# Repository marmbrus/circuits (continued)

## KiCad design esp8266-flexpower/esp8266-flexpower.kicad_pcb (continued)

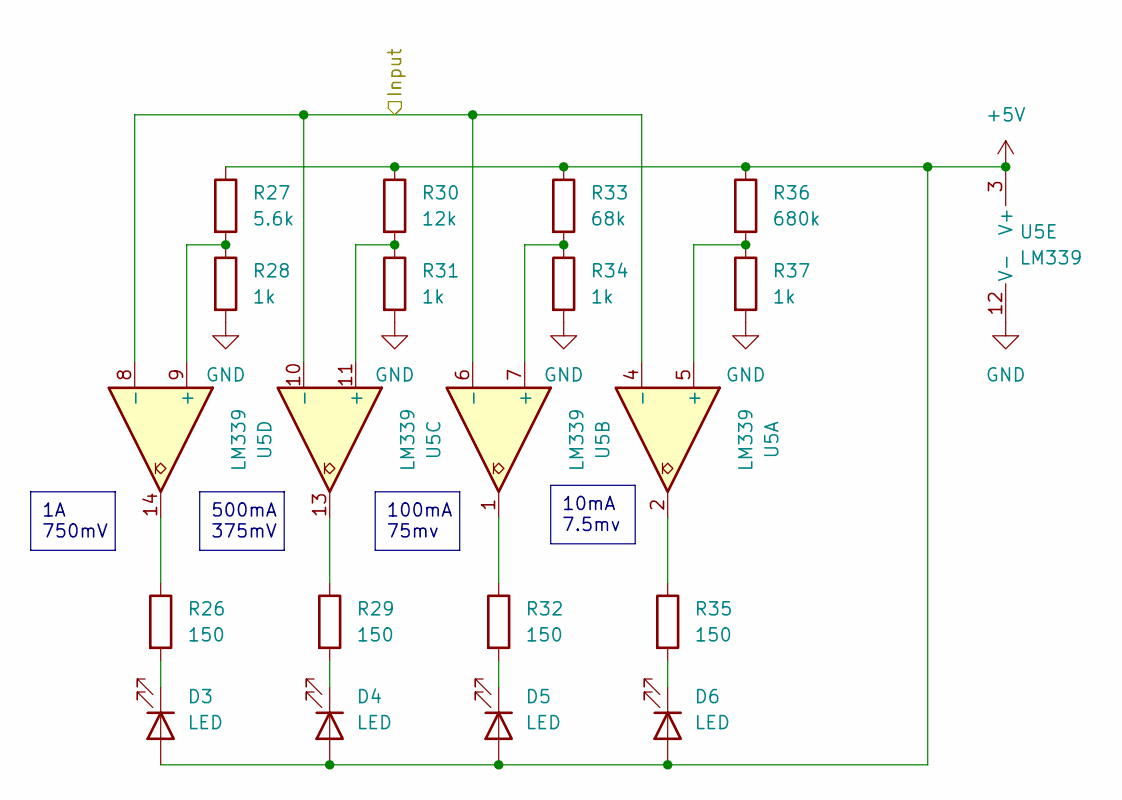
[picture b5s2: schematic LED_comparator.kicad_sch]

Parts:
D3, D4, D5, D6: LED; LED_0603_1608Metric; LCSC Part C2286
R26, R29, R32, R35: 150; R_0603_1608Metric
R27: 5.6k; R_0603_1608Metric
R28, R31, R34, R37: 1k; R_0603_1608Metric
R30: 12k; R_0603_1608Metric
R33: 68k; R_0603_1608Metric
R36: 680k; R_0603_1608Metric
U5: LM339; SOIC-14_3.9x8.7mm_P1.27mm; LCSC Part C350549

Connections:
+5V: D3.2 (A), D4.2 (A), D5.2 (A), D6.2 (A), R27.1, R30.1, R33.1, R36.1, U5.3 (V+); also elsewhere on the board
/LEDComparator/Input: U5.4 (-), U5.6 (-), U5.8 (-), U5.10 (-); also elsewhere on the board
GND: R28.2, R31.2, R34.2, R37.2, U5.12 (V-); also elsewhere on the board
unnamed: D3.1 (K), R26.2
unnamed: D4.1 (K), R29.2
unnamed: D5.1 (K), R32.2
unnamed: D6.1 (K), R35.2
unnamed: R26.1, U5.14
unnamed: R29.1, U5.13
unnamed: R32.1, U5.1
unnamed: R35.1, U5.2
unnamed: R36.2, R37.1, U5.5 (+)
unnamed: R33.2, R34.1, U5.7 (+)
unnamed: R30.2, R31.1, U5.11 (+)
unnamed: R27.2, R28.1, U5.9 (+)

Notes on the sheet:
1A 750mV
100mA 75mv
10mA 7.5mv
500mA 375mV

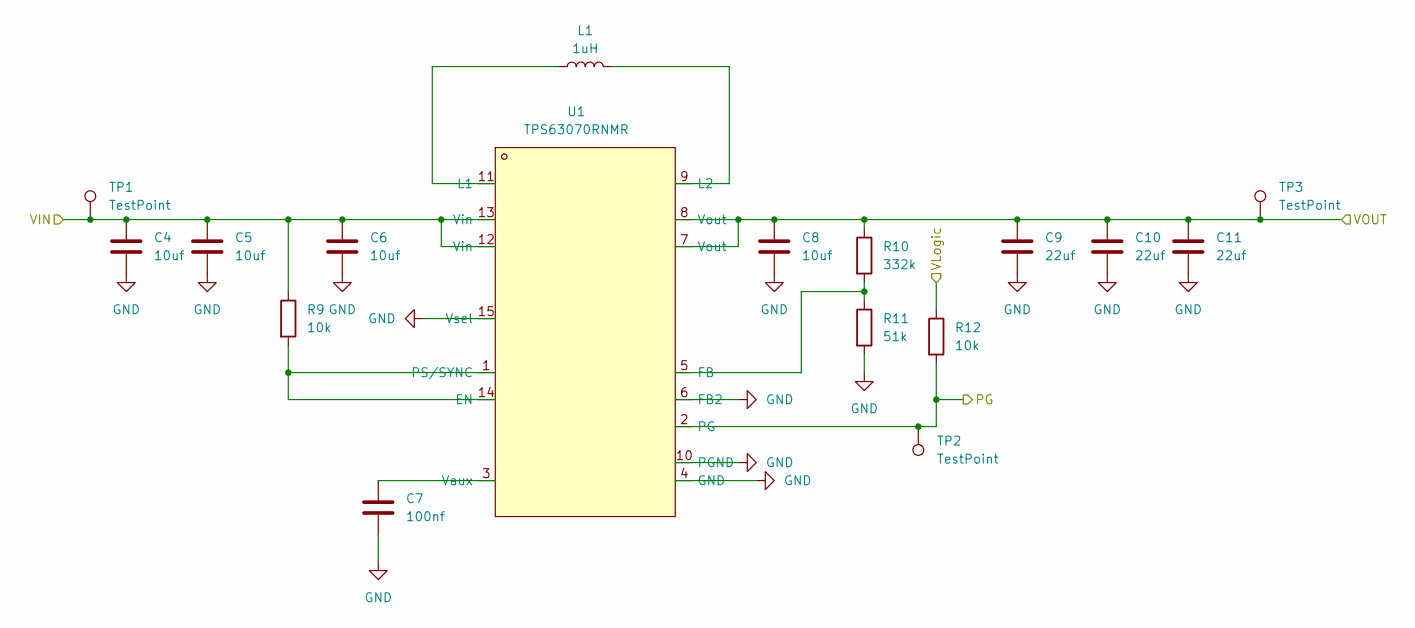
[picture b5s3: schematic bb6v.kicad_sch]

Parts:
C4, C5: 10uf; C_0805_2012Metric
C6, C8: 10uf; C_0603_1608Metric
C7: 100nf; C_0603_1608Metric
C9, C10, C11: 22uf; C_0805_2012Metric
L1: 1uH; L_Coilcraft_XAL4020-XXX; LCSC Part C4555951
R9, R12: 10k; R_0603_1608Metric
R10: 332k; R_0603_1608Metric
R11: 51k; R_0603_1608Metric
TP1, TP2, TP3: TestPoint; Pin_D1.0mm_L10.0mm
U1: TPS63070RNMR; VQFN-HR-15_L3.0-W2.5-P0.50-BL_TPS63070RNMR; LCSC Part C109322

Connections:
+5V: R12.1; also elsewhere on the board
/33Reg/VIN: C8.1, C9.1, C10.1, C11.1, R10.1, TP3.1, U1.7 (Vout), U1.8 (Vout); also elsewhere on the board
/BB6V/PG: R12.2, TP2.1, U1.2 (PG)
/BB6V/VIN: C4.1, C5.1, C6.1, R9.1, TP1.1, U1.12 (Vin), U1.13 (Vin); also elsewhere on the board
GND: C4.2, C5.2, C6.2, C7.2, C8.2, C9.2, C10.2, C11.2, R11.2, U1.4 (GND), U1.6 (FB2), U1.10 (PGND), U1.15 (Vsel); also elsewhere on the board
unnamed: R9.2, U1.1 (PS/SYNC), U1.14 (EN)
unnamed: R10.2, R11.1, U1.5 (FB)
unnamed: L1.1, U1.11 (L1)
unnamed: L1.2, U1.9 (L2)
unnamed: C7.1, U1.3 (Vaux)

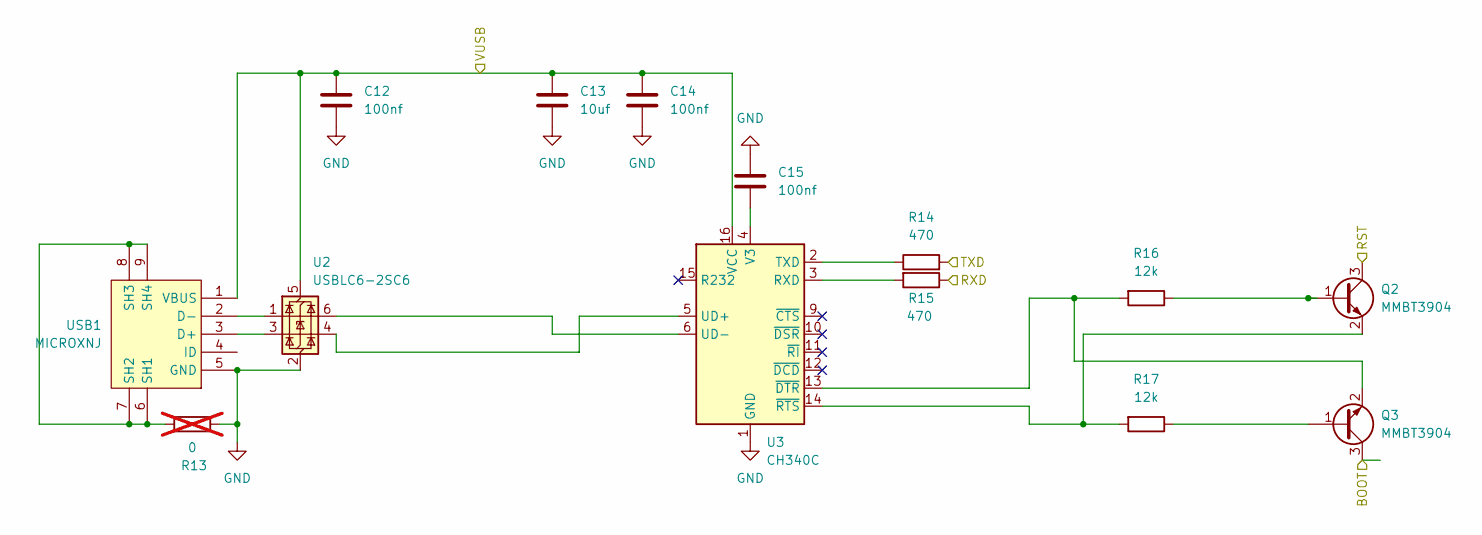
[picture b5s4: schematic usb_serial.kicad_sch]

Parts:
C12, C14, C15: 100nf; C_0603_1608Metric
C13: 10uf; C_0603_1608Metric
Q2, Q3: MMBT3904; SOT-23
R13: 0; R_0603_1608Metric; not fitted
R14, R15: 470; R_0603_1608Metric
R16, R17: 12k; R_0603_1608Metric
U2: USBLC6-2SC6; SOT-23-6
U3: CH340C; SOIC-16_3.9x9.9mm_P1.27mm
USB1: MICROXNJ; MICRO-USB-SMD_MICROXNJ; LCSC Part C404969

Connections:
/ESP12F/BOOT: Q3.3 (C); also elsewhere on the board
/ESP12F/RST: Q2.3 (C); also elsewhere on the board
/ESP12F/RXD: R14.2; also elsewhere on the board
/ESP12F/TXD: R15.1; also elsewhere on the board
/PP3V16V/VIN: C12.1, C13.1, C14.1, U2.5 (VBUS), U3.16 (VCC), USB1.1 (VBUS); also elsewhere on the board
GND: C12.2, C13.2, C14.2, C15.1, R13.2, U2.2 (GND), U3.1 (GND), USB1.5 (GND); also elsewhere on the board
unnamed: Q2.1 (B), R16.1
unnamed: Q2.2 (E), R17.2, U3.14 (~RTS)
unnamed: Q3.1 (B), R17.1
unnamed: Q3.2 (E), R16.2, U3.13 (~DTR)
unnamed: R15.2, U3.3 (RXD)
unnamed: R14.1, U3.2 (TXD)
unnamed: U2.4 (I/O2), U3.5 (UD+)
unnamed: U2.6 (I/O1), U3.6 (UD-)
unnamed: C15.2, U3.4 (V3)
unnamed: U2.3 (I/O2), USB1.3 (D+)
unnamed: U2.1 (I/O1), USB1.2 (D-)
unnamed: R13.1, USB1.6 (SH1), USB1.7 (SH2), USB1.8 (SH3), USB1.9 (SH4)

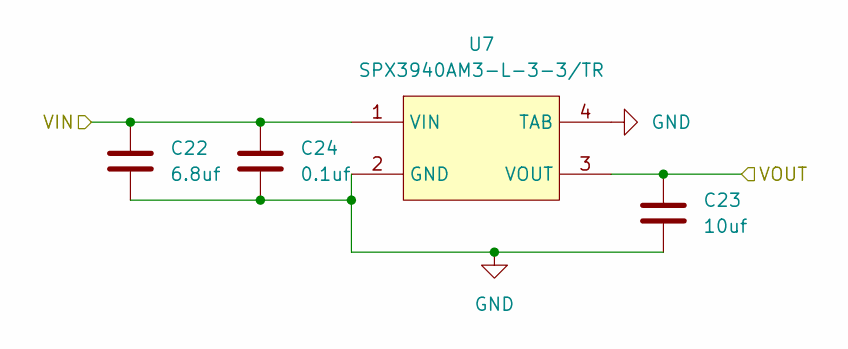
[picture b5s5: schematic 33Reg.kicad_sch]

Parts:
C22: 6.8uf; C_0603_1608Metric
C23: 10uf; C_0603_1608Metric
C24: 0.1uf; C_0603_1608Metric
U7: SPX3940AM3-L-3-3/TR; SOT-223-3_L6.5-W3.4-P2.30-LS7.0-BR; LCSC Part C48252

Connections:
/33Reg/VIN: C22.1, C24.1, U7.1 (VIN); also elsewhere on the board
/33Reg/VOUT: C23.1, U7.3 (VOUT); also elsewhere on the board
GND: C22.2, C23.2, C24.2, U7.2 (GND), U7.4 (TAB); also elsewhere on the board

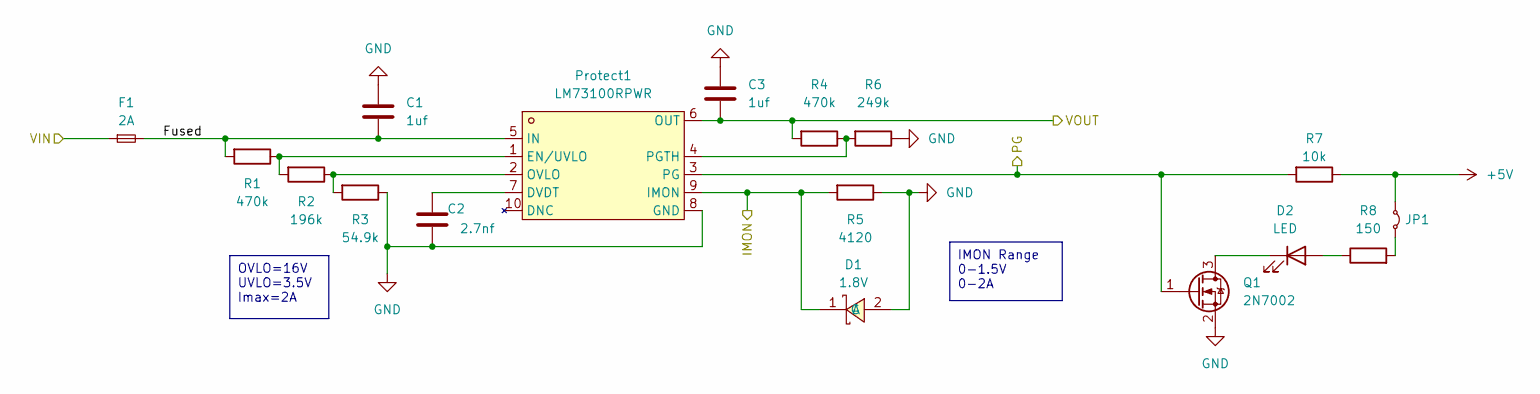
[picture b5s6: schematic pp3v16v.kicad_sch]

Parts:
C1, C3: 1uf; C_0603_1608Metric
C2: 2.7nf; C_0603_1608Metric
D1: 1.8V; SOD-123_L2.7-W1.6-LS3.7-RD; LCSC Part C150464
D2: LED; LED_0603_1608Metric; LCSC Part C2286
F1: 2A; Fuse_1206_3216Metric; LCSC Part C2924939
JP1: JP1; SolderJumper-2_P1.3mm_Bridged_Pad1.0x1.5mm
Protect1: LM73100RPWR; VQFN-10_L2.0-W2.0-P0.45-TL; LCSC Part C3210761
Q1: 2N7002; SOT-23
R1, R4: 470k; R_0603_1608Metric
R2: 196k; R_0603_1608Metric
R3: 54.9k; R_0603_1608Metric
R5: 4120; R_0603_1608Metric
R6: 249k; R_0603_1608Metric
R7: 10k; R_0603_1608Metric
R8: 150; R_0603_1608Metric

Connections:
+5V: JP1.1 (A), R7.1; also elsewhere on the board
/BB6V/VIN: C3.2, Protect1.6 (OUT), R4.2; also elsewhere on the board
/PP3V16V/Fused: C1.2, F1.2, Protect1.5 (IN), R1.2
/PP3V16V/IMON: D1.1 (C), Protect1.9 (IMON), R5.2
/PP3V16V/PG: Protect1.3 (PG), Q1.1 (G), R7.2
/PP3V16V/VIN: F1.1; also elsewhere on the board
GND: C1.1, C2.2, C3.1, D1.2 (A), Protect1.8 (GND), Q1.2 (S), R3.1, R5.1, R6.1; also elsewhere on the board
unnamed: D2.2 (A), R8.1
unnamed: D2.1 (K), Q1.3 (D)
unnamed: JP1.2 (B), R8.2
unnamed: C2.1, Protect1.7 (DVDT)
unnamed: Protect1.1 (EN/UVLO), R1.1, R2.2
unnamed: Protect1.2 (OVLO), R2.1, R3.2
unnamed: Protect1.4 (PGTH), R4.1, R6.2

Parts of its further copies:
C19, C21: 1uf; C_0603_1608Metric
C20: 2.7nf; C_0603_1608Metric
D7: 1.8V; SOD-123_L2.7-W1.6-LS3.7-RD; LCSC Part C150464
D8: LED; LED_0603_1608Metric; LCSC Part C2286
F2: 2A; Fuse_1206_3216Metric; LCSC Part C2924939
JP2: JP1; SolderJumper-2_P1.3mm_Bridged_Pad1.0x1.5mm
Protect2: LM73100RPWR; VQFN-10_L2.0-W2.0-P0.45-TL; LCSC Part C3210761
Q4: 2N7002; SOT-23
R38, R41: 470k; R_0603_1608Metric
R39: 196k; R_0603_1608Metric
R40: 54.9k; R_0603_1608Metric
R42: 4120; R_0603_1608Metric
R43: 249k; R_0603_1608Metric
R44: 10k; R_0603_1608Metric
R45: 150; R_0603_1608Metric

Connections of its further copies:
+5V: JP2.1 (A), R44.1; also elsewhere on the board
/BB6V/VIN: C21.2, Protect2.6 (OUT), R41.2; also elsewhere on the board
/LEDComparator/Input: D7.1 (C), Protect2.9 (IMON), R42.2; also elsewhere on the board
/PP3V16V1/Fused: C19.2, F2.2, Protect2.5 (IN), R38.2
/PP3V16V1/PG: Protect2.3 (PG), Q4.1 (G), R44.2
/PP3V16V1/VIN: F2.1; also elsewhere on the board
GND: C19.1, C20.2, C21.1, D7.2 (A), Protect2.8 (GND), Q4.2 (S), R40.1, R42.1, R43.1; also elsewhere on the board
unnamed: D8.2 (A), R45.1
unnamed: D8.1 (K), Q4.3 (D)
unnamed: JP2.2 (B), R45.2
unnamed: C20.1, Protect2.7 (DVDT)
unnamed: Protect2.1 (EN/UVLO), R38.1, R39.2
unnamed: Protect2.2 (OVLO), R39.1, R40.2
unnamed: Protect2.4 (PGTH), R41.1, R43.2

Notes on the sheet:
IMON Range 0-1.5V 0-2A
OVLO=16V UVLO=3.5V Imax=2A

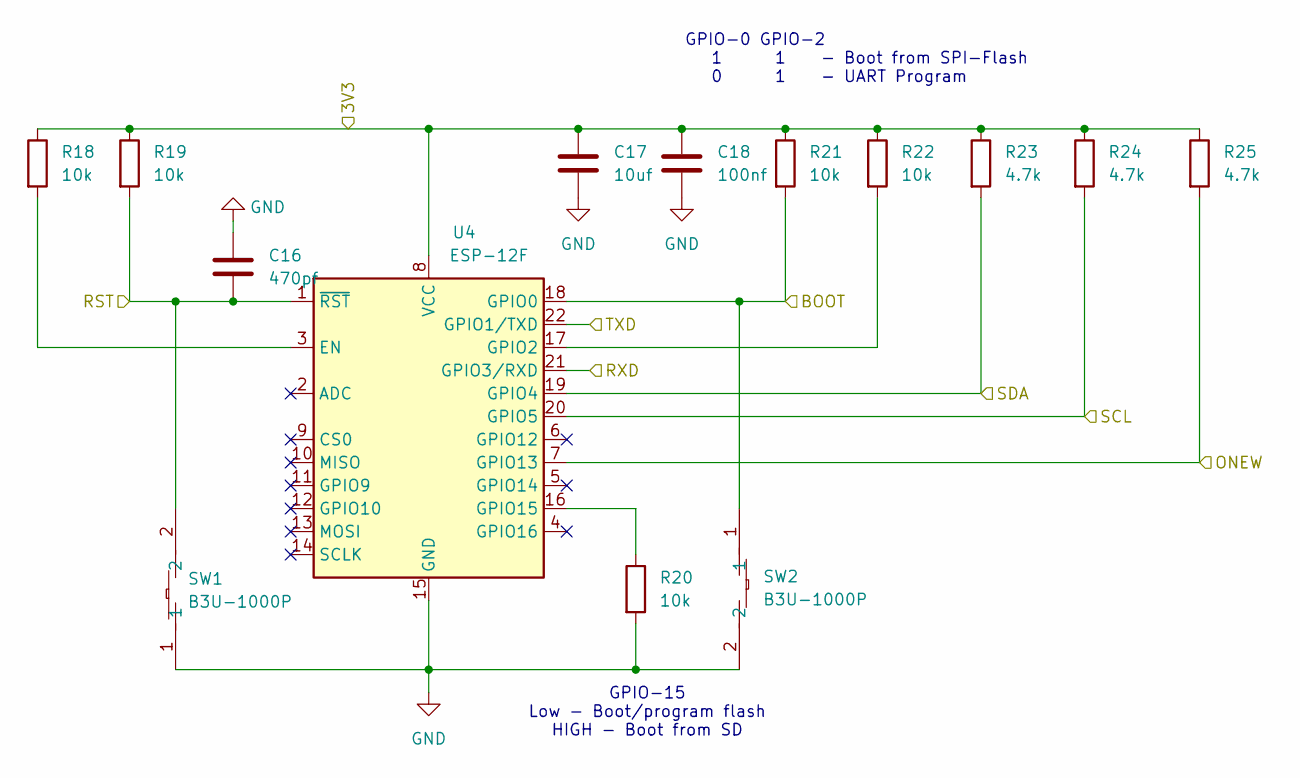
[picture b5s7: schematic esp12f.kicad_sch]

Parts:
C16: 470pf; C_0603_1608Metric
C17: 10uf; C_0603_1608Metric
C18: 100nf; C_0603_1608Metric
R18, R19, R20, R21, R22: 10k; R_0603_1608Metric
R23, R24, R25: 4.7k; R_0603_1608Metric
SW1, SW2: B3U-1000P; KEY-SMD_B3U-1000PM; LCSC Part C231329
U4: ESP-12F; ESP-12E

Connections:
/33Reg/VOUT: C17.1, C18.1, R18.1, R19.1, R21.1, R22.1, R23.1, R24.1, R25.1, U4.8 (VCC); also elsewhere on the board
/ESP12F/BOOT: R21.2, SW2.1, U4.18 (GPIO0); also elsewhere on the board
/ESP12F/ONEW: R25.2, U4.7 (GPIO13); also elsewhere on the board
/ESP12F/RST: C16.2, R19.2, SW1.2, U4.1 (~RST); also elsewhere on the board
/ESP12F/RXD: U4.21 (GPIO3/RXD); also elsewhere on the board
/ESP12F/SCL: R24.2, U4.20 (GPIO5); also elsewhere on the board
/ESP12F/SDA: R23.2, U4.19 (GPIO4); also elsewhere on the board
/ESP12F/TXD: U4.22 (GPIO1/TXD); also elsewhere on the board
GND: C16.1, C17.2, C18.2, R20.2, SW1.1, SW2.2, U4.15 (GND); also elsewhere on the board
unnamed: R18.2, U4.3 (EN)
unnamed: R22.2, U4.17 (GPIO2)
unnamed: R20.1, U4.16 (GPIO15)

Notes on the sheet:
GPIO-15 Low - Boot/program flash HIGH - Boot from SD
GPIO-0 GPIO-2 1 1 - Boot from SPI-Flash 0 1 - UART Program

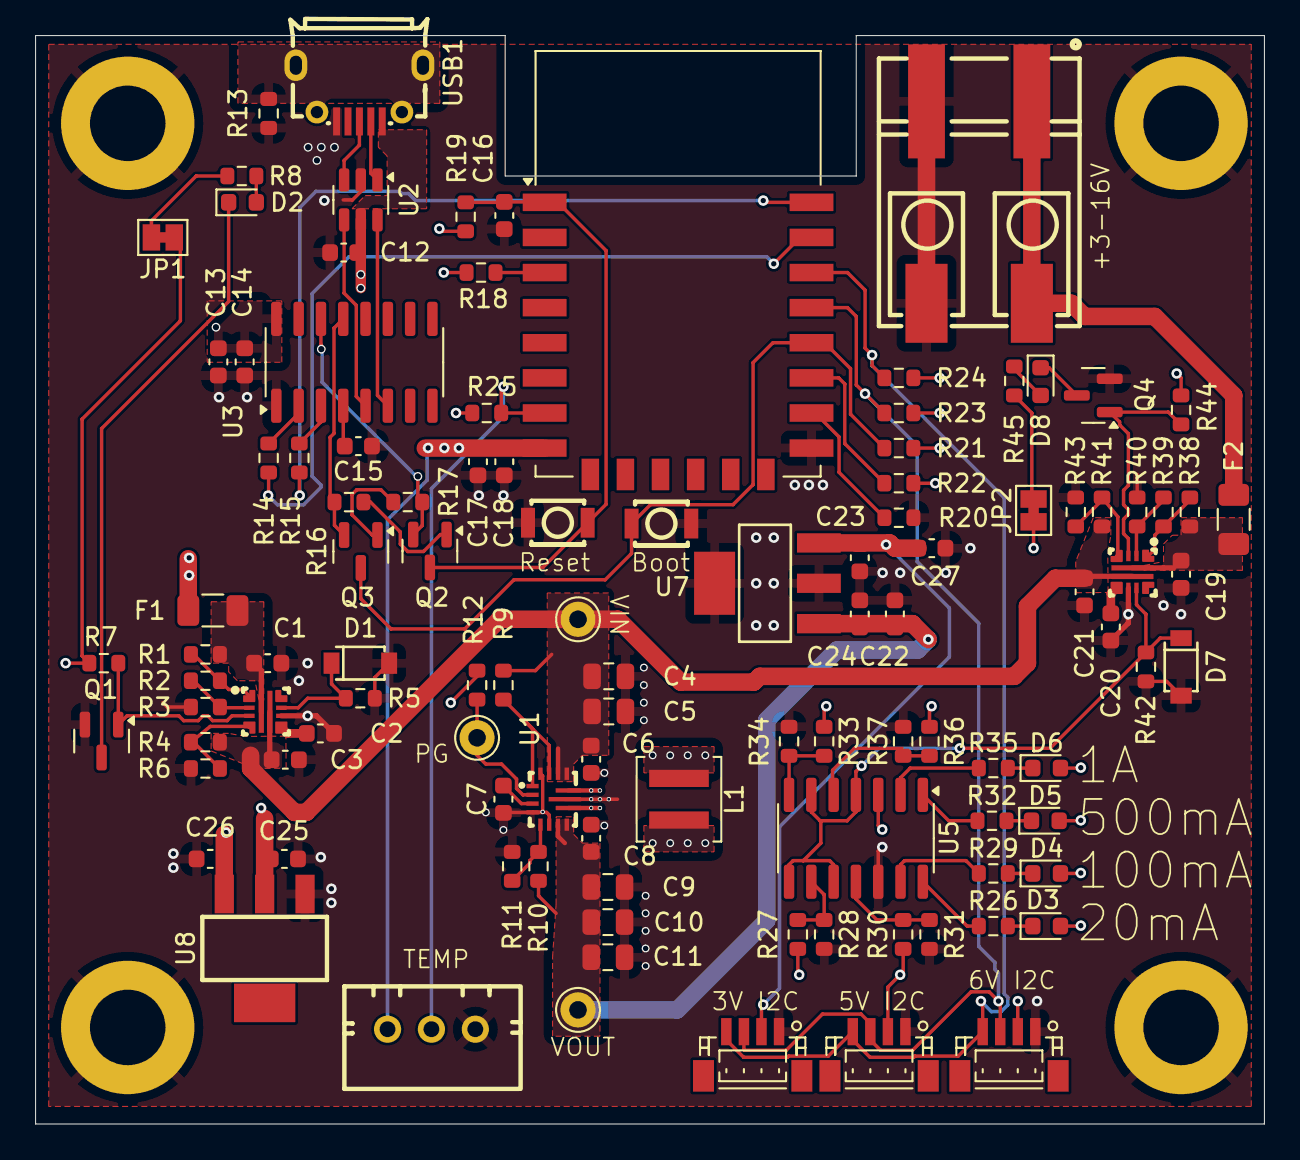
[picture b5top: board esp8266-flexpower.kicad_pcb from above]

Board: 4 copper layers, 70.0 x 62.0 mm, 113 parts (0 on the bottom side), 67 nets.

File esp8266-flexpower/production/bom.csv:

Designator,Footprint,Quantity,Value,LCSC Part #
"C1, C19, C21, C3",0603,4,1uf,
"C10, C11, C9",0805,3,22uf,
"C12, C14, C15, C18, C7",0603,5,100nf,
"C13, C17, C23, C25, C26, C6, C8",0603,7,10uf,
C16,0603,1,470pf,
"C2, C20",0603,2,2.7nf,
C22,0603,1,6.8uf,
C24,0603,1,0.1uf,
C27,0603,1,47uf,
"C4, C5",0805,2,10uf,
"CN1, CN2, CN3",CONN-SMD_BM04B-SRSS-TB,3,BM04B-SRSS-TB(LF)(SN),C160390
"D1, D7",SOD-123_L2.7-W1.6-LS3.7-RD,2,1.8V,C150464
"D2, D3, D4, D5, D6, D8",0603,6,LED,C2286
"F1, F2",1206,2,2A,C2924939
"JP1, JP2",SolderJumper-2_P1.3mm_Bridged_Pad1.0x1.5mm,2,JP1,
L1,L_Coilcraft_XAL4020-XXX,1,1uH,C4555951
"Protect1, Protect2",VQFN-10_L2.0-W2.0-P0.45-TL,2,LM73100RPWR,C3210761
"Q1, Q4",SOT-23,2,2N7002,
"Q2, Q3",SOT-23,2,MMBT3904,
"R1, R38, R4, R41",0603,4,470k,
R10,0603,1,332k,
R11,0603,1,51k,
"R12, R18, R19, R20, R21, R22, R44, R7, R9",0603,9,10k,
"R14, R15",0603,2,470,
"R16, R17, R30",0603,3,12k,
"R2, R39",0603,2,196k,
"R23, R24, R25",0603,3,4.7k,
"R26, R29, R32, R35, R45, R8",0603,6,150,
R27,0603,1,5.6k,
"R28, R31, R34, R37",0603,4,1k,
"R3, R40",0603,2,54.9k,
R33,0603,1,68k,
R36,0603,1,680k,
"R42, R5",0603,2,4120,
"R43, R6",0603,2,249k,
"SW1, SW2",KEY-SMD_B3U-1000PM,2,B3U-1000P,C231329
U1,VQFN-HR-15_L3.0-W2.5-P0.50-BL_TPS63070RNMR,1,TPS63070RNMR,C109322
U2,SOT-23-6,1,USBLC6-2SC6,
U3,SOIC-16_3.9x9.9mm_P1.27mm,1,CH340C,
U4,ESP-12E,1,ESP-12F,
U5,SOIC-14_3.9x8.7mm_P1.27mm,1,LM339,C350549
U6,CONN-SMD_2061-602-998-404,1,2061-602/998-404,C2765058
U7,SOT-223-3_L6.5-W3.4-P2.30-LS7.0-BR,1,SPX3940AM3-L-3-3/TR,C48252
U8,SOT-223_L6.7-W3.5-P2.30-BR,1,AMS1117-5.0_C347223,C347223
U9,CONN-TH_3P-P2.50_A2501WV2-3P,1,B3B-XH-A(LF)(SN),C144394
USB1,MICRO-USB-SMD_MICROXNJ,1,MICROXNJ,C404969

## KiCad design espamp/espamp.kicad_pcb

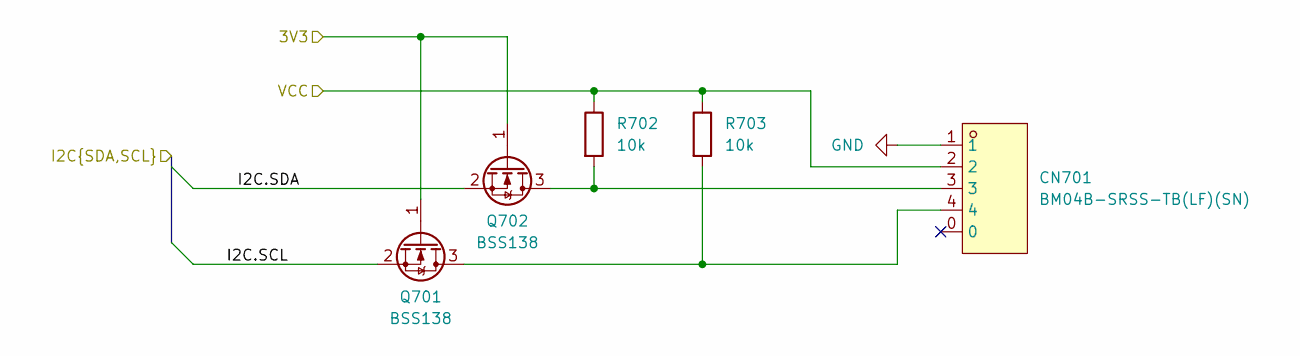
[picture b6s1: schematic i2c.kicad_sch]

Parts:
CN701: BM04B-SRSS-TB(LF)(SN); CONN-SMD_BM04B-SRSS-TB; LCSC Part C160390
Q701, Q702: BSS138; SOT-23
R702, R703: 10k; R_0603_1608Metric

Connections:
/3v3/3v3: Q701.1 (G), Q702.1 (G); also elsewhere on the board
/5V: CN701.2, R702.1, R703.1; also elsewhere on the board
/amp/I2C.SCL: Q701.2 (S); also elsewhere on the board
/amp/I2C.SDA: Q702.2 (S); also elsewhere on the board
GND: CN701.1; also elsewhere on the board
unnamed: CN701.4, Q701.3 (D), R703.2
unnamed: CN701.3, Q702.3 (D), R702.2

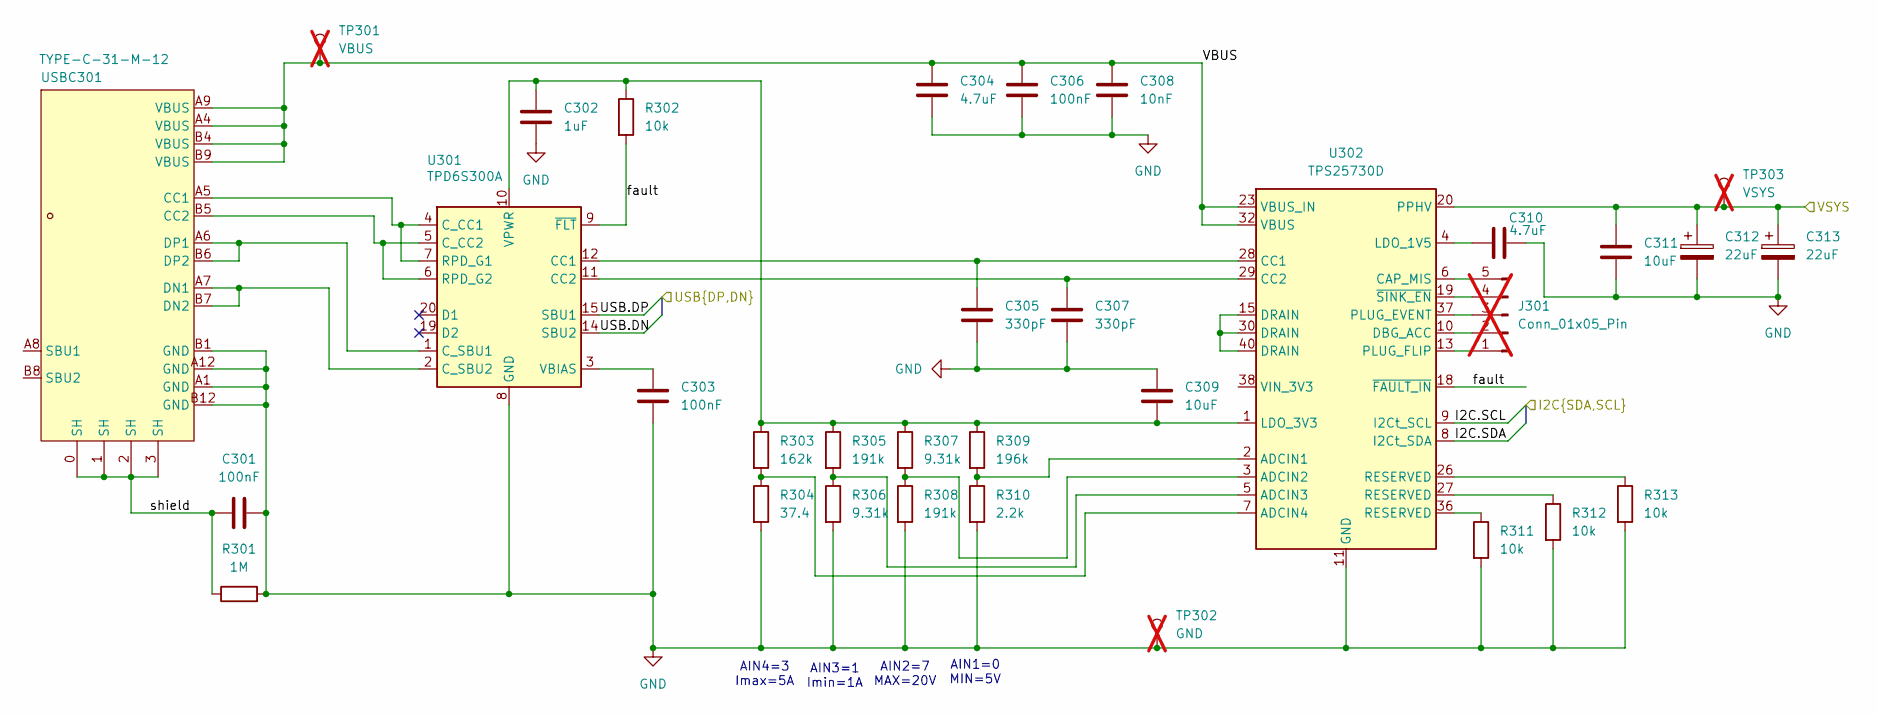
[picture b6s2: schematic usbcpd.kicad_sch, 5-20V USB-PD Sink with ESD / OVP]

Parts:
C301, C303, C306: 100nF; C_0603_1608Metric
C302: 1uF; C_0603_1608Metric
C304, C310: 4.7uF; C_0603_1608Metric
C305, C307: 330pF; C_0603_1608Metric
C308: 10nF; C_0603_1608Metric
C309, C311: 10uF; C_0603_1608Metric
C312, C313: 22uF; C_Elec_5x5.8; LCSC Part C336246
J301: Conn_01x05_Pin; PinSocket_1x05_P1.00mm_Vertical; not fitted
R301: 1M; R_0603_1608Metric
R302, R311, R312, R313: 10k; R_0603_1608Metric
R303: 162k; R_0603_1608Metric
R304: 37.4; R_0603_1608Metric
R305, R308: 191k; R_0603_1608Metric
R306, R307: 9.31k; R_0603_1608Metric
R309: 196k; R_0603_1608Metric
R310: 2.2k; R_0603_1608Metric
TP301: VBUS; Pin_D1.0mm_L10.0mm; not fitted
TP302: GND; Pin_D1.0mm_L10.0mm; not fitted
TP303: VSYS; Pin_D1.0mm_L10.0mm; not fitted
U301: TPD6S300A; WQFN-20-1EP_3x3mm_P0.4mm_EP1.7x1.7mm_ThermalVias
U302: TPS25730D; Texas_REF0038A_WQFN-38-2EP_6x4mm_P0.4
USBC301: TYPE-C-31-M-12; USB-C_SMD-TYPE-C-31-M-12; LCSC Part C165948

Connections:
/20V: C311.1, C312.1, C313.1, TP303.1, U302.20 (PPHV); also elsewhere on the board
/amp/I2C.SCL: U302.9 (I2Ct_SCL); also elsewhere on the board
/amp/I2C.SDA: U302.8 (I2Ct_SDA); also elsewhere on the board
/esp32/USB.DN: U301.14 (SBU2); also elsewhere on the board
/esp32/USB.DP: U301.15 (SBU1); also elsewhere on the board
/usbcpd/VBUS: C304.1, C306.1, C308.1, TP301.1, U302.23 (VBUS_IN), U302.32 (VBUS), USBC301.A4 (VBUS), USBC301.A9 (VBUS), USBC301.B4 (VBUS), USBC301.B9 (VBUS)
/usbcpd/fault: R302.2, U301.9 (~FLT), U302.18 (~FAULT_IN)
/usbcpd/shield: C301.1, R301.1, USBC301.0 (SH), USBC301.1 (SH), USBC301.2 (SH), USBC301.3 (SH)
GND: C301.2, C302.2, C303.2, C304.2, C305.2, C306.2, C307.2, C308.2, C309.2, C310.2, C311.2, C312.2, C313.2, R301.2, R304.2, R306.2, R308.2, R310.2, R311.2, R312.2, R313.2, TP302.1, U301.8 (GND), U301.13 (GND), U301.16 (GND), U301.17 (GND), U301.18 (GND), U301.21 (GND), U302.11 (GND), U302.12 (GND), U302.14 (GND), U302.16 (GND), U302.17 (GND), U302.31 (GND), U302.34 (GND), U302.39 (GND), USBC301.A1 (GND), USBC301.A12 (GND), USBC301.B1 (GND), USBC301.B12 (GND); also elsewhere on the board
unnamed: J301.1, U302.13 (PLUG_FLIP)
unnamed: J301.2, U302.10 (DBG_ACC)
unnamed: J301.3, U302.37 (PLUG_EVENT)
unnamed: J301.4, U302.19 (~SINK_EN)
unnamed: J301.5, U302.6 (CAP_MIS)
unnamed: R311.1, U302.36 (RESERVED)
unnamed: R312.1, U302.27 (RESERVED)
unnamed: R313.1, U302.26 (RESERVED)
unnamed: C305.1, U301.12 (CC1), U302.28 (CC1)
unnamed: C307.1, U301.11 (CC2), U302.29 (CC2)
unnamed: U301.4 (C_CC1), U301.7 (RPD_G1), USBC301.A5 (CC1)
unnamed: U301.5 (C_CC2), U301.6 (RPD_G2), USBC301.B5 (CC2)
unnamed: U301.1 (C_SBU1), USBC301.A6 (DP1), USBC301.B6 (DP2)
unnamed: U301.2 (C_SBU2), USBC301.A7 (DN1), USBC301.B7 (DN2)
unnamed: C303.1, U301.3 (VBIAS)
unnamed: C302.1, C309.1, R302.1, R303.1, R305.1, R307.1, R309.1, U301.10 (VPWR), U302.1 (LDO_3V3)
unnamed: R309.2, R310.1, U302.2 (ADCIN1)
unnamed: R307.2, R308.1, U302.3 (ADCIN2)
unnamed: R305.2, R306.1, U302.5 (ADCIN3)
unnamed: R303.2, R304.1, U302.7 (ADCIN4)
unnamed: U302.15 (DRAIN), U302.30 (DRAIN), U302.40 (DRAIN)
unnamed: C310.1, U302.4 (LDO_1V5)

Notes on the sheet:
AIN1=0 MIN=5V
AIN3=1 Imin=1A
AIN4=3 Imax=5A
AIN2=7 MAX=20V

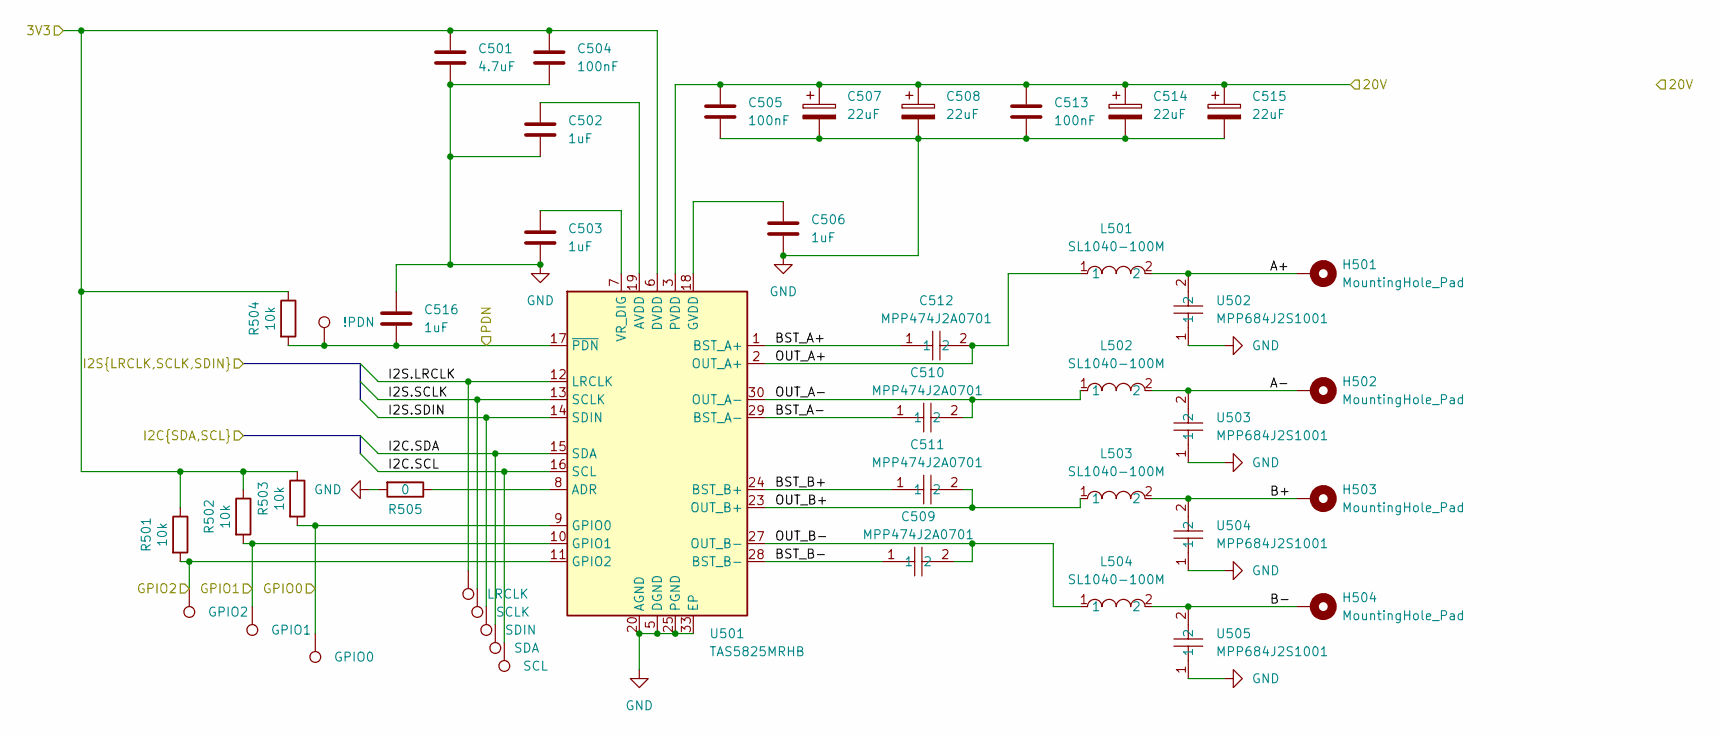
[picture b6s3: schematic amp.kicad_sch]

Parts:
C501: 4.7uF; C_0603_1608Metric
C502, C503, C506, C516: 1uF; C_0603_1608Metric
C504, C505, C513: 100nF; C_0603_1608Metric
C507, C508, C514, C515: 22uF; C_Elec_5x5.8; LCSC Part C336246
C509, C510, C511, C512: MPP474J2A0701; CAP-TH_L9.5-W3.7-P7.50-D0.5; LCSC Part C3019096
H501, H502, H503, H504: MountingHole_Pad; MountingHole_4mm_Pad_Via
L501, L502, L503, L504: SL1040-100M; IND-SMD_L11.0-W10.2; LCSC Part C22463839
R501, R502, R503, R504: 10k; R_0603_1608Metric
R505: 0; R_0603_1608Metric
TP501, TP502, TP503, TP504, TP505, TP506, TP507, TP508, TP509: LabeledTestPoint
U501: TAS5825MRHB; VQFN-32-1EP_5x5mm_P0.5mm_EP3.1x3.1mm
U502, U503, U504, U505: MPP684J2S1001; CAP-TH_L12.0-W5.8-P10.00-D0.6; LCSC Part C3019017

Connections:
/3v3/3v3: C501.1, C504.1, R501.1, R502.1, R503.1, R504.1, U501.6 (DVDD); also elsewhere on the board
/20V: C505.1, C507.1, C508.1, C513.1, C514.1, C515.1, U501.3 (PVDD), U501.4 (PVDD), U501.21 (PVDD), U501.22 (PVDD); also elsewhere on the board
/amp/A+: H501.1, L501.2, U502.2
/amp/A-: H502.1, L502.2, U503.2
/amp/B+: H503.1, L503.2, U504.2
/amp/B-: H504.1, L504.2, U505.2
/amp/BST_A+: C512.1, U501.1 (BST_A+)
/amp/BST_A-: C510.1, U501.29 (BST_A-)
/amp/BST_B+: C511.1, U501.24 (BST_B+)
/amp/BST_B-: C509.1, U501.28 (BST_B-)
/amp/GPIO0: R503.2, TP503.1, U501.9 (GPIO0); also elsewhere on the board
/amp/GPIO1: R502.2, TP502.1, U501.10 (GPIO1); also elsewhere on the board
/amp/GPIO2: R501.2, TP501.1, U501.11 (GPIO2); also elsewhere on the board
/amp/I2C.SCL: TP508.1, U501.16 (SCL); also elsewhere on the board
/amp/I2C.SDA: TP507.1, U501.15 (SDA); also elsewhere on the board
/amp/I2S.LRCLK: TP504.1, U501.12 (LRCLK); also elsewhere on the board
/amp/I2S.SCLK: TP505.1, U501.13 (SCLK); also elsewhere on the board
/amp/I2S.SDIN: TP506.1, U501.14 (SDIN); also elsewhere on the board
/amp/OUT_A+: C512.2, L501.1, U501.2 (OUT_A+)
/amp/OUT_A-: C510.2, L502.1, U501.30 (OUT_A-)
/amp/OUT_B+: C511.2, L503.1, U501.23 (OUT_B+)
/amp/OUT_B-: C509.2, L504.1, U501.27 (OUT_B-)
/amp/PDN: C516.2, R504.2, TP509.1, U501.17 (~PDN); also elsewhere on the board
GND: C501.2, C502.2, C503.2, C504.2, C505.2, C506.2, C507.2, C508.2, C513.2, C514.2, C515.2, C516.1, R505.2, U501.5 (DGND), U501.20 (AGND), U501.25 (PGND), U501.26 (PGND), U501.31 (PGND), U501.32 (PGND), U501.33 (EP), U502.1, U503.1, U504.1, U505.1; also elsewhere on the board
unnamed: R505.1, U501.8 (ADR)
unnamed: C502.1, U501.19 (AVDD)
unnamed: C506.1, U501.18 (GVDD)
unnamed: C503.1, U501.7 (VR_DIG)

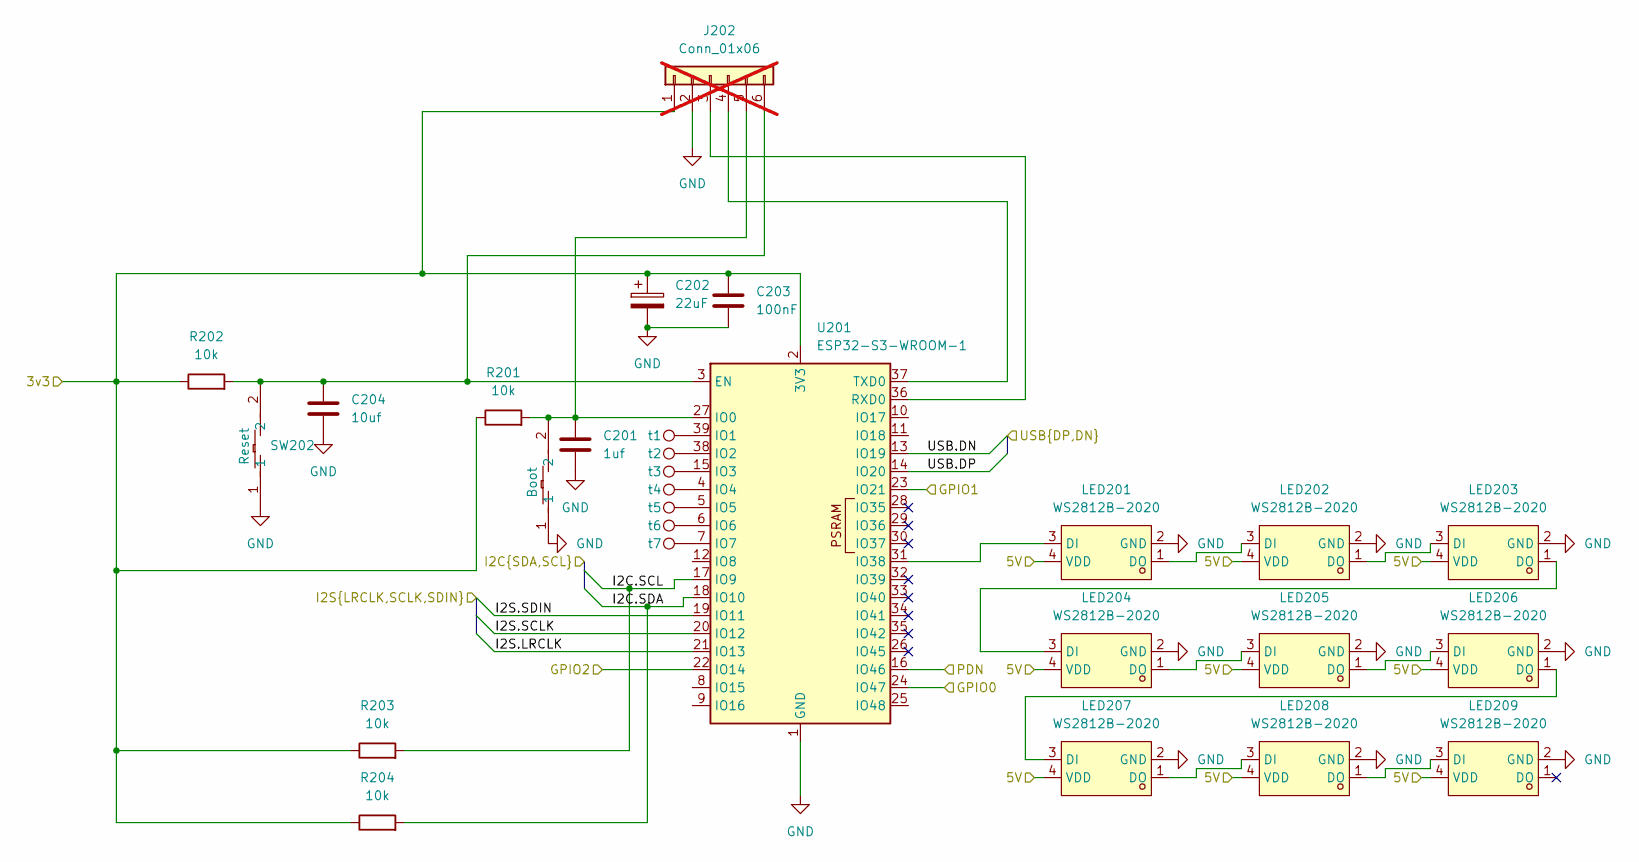
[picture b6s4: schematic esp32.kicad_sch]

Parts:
C201: 1uf; C_0603_1608Metric
C202: 22uF; C_Elec_5x5.8; LCSC Part C336246
C203: 100nF; C_0603_1608Metric
C204: 10uf; C_0603_1608Metric
J202: Conn_01x06; PinHeader_1x06_P2.54mm_Vertical; not fitted
LED201, LED202, LED203, LED204, LED205, LED206, LED207, LED208, LED209: WS2812B-2020; LED-SMD_4P-L2.0-W2.0-TL_WS2812B-2020; LCSC Part C965555
R201, R202, R203, R204: 10k; R_0603_1608Metric
SW201, SW202: KEY-SMD_B3U-1000PM; LCSC Part C231329
TP201, TP202, TP203, TP204, TP205, TP206, TP207: LabeledTestPoint
U201: ESP32-S3-WROOM-1

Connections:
/3v3/3v3: C202.1, C203.1, J202.1, R201.1, R202.1, R203.1, R204.1, U201.2 (3V3); also elsewhere on the board
/5V: LED201.4 (VDD), LED202.4 (VDD), LED203.4 (VDD), LED204.4 (VDD), LED205.4 (VDD), LED206.4 (VDD), LED207.4 (VDD), LED208.4 (VDD), LED209.4 (VDD); also elsewhere on the board
/amp/GPIO0: U201.24 (IO47); also elsewhere on the board
/amp/GPIO1: U201.23 (IO21); also elsewhere on the board
/amp/GPIO2: U201.22 (IO14); also elsewhere on the board
/amp/I2C.SCL: R203.2, U201.17 (IO9); also elsewhere on the board
/amp/I2C.SDA: R204.2, U201.18 (IO10); also elsewhere on the board
/amp/I2S.LRCLK: U201.21 (IO13); also elsewhere on the board
/amp/I2S.SCLK: U201.20 (IO12); also elsewhere on the board
/amp/I2S.SDIN: U201.19 (IO11); also elsewhere on the board
/amp/PDN: U201.16 (IO46); also elsewhere on the board
/esp32/USB.DN: U201.13 (IO19); also elsewhere on the board
/esp32/USB.DP: U201.14 (IO20); also elsewhere on the board
GND: C201.2, C202.2, C203.2, C204.2, J202.2, LED201.2 (GND), LED202.2 (GND), LED203.2 (GND), LED204.2 (GND), LED205.2 (GND), LED206.2 (GND), LED207.2 (GND), LED208.2 (GND), LED209.2 (GND), SW201.1, SW202.1, U201.1 (GND), U201.40 (GND), U201.41 (GND); also elsewhere on the board
unnamed: J202.3, U201.36 (RXD0)
unnamed: J202.4, U201.37 (TXD0)
unnamed: C201.1, J202.5, R201.2, SW201.2, U201.27 (IO0)
unnamed: C204.1, J202.6, R202.2, SW202.2, U201.3 (EN)
unnamed: LED201.3 (DI), U201.31 (IO38)
unnamed: LED201.1 (DO), LED202.3 (DI)
unnamed: LED202.1 (DO), LED203.3 (DI)
unnamed: LED203.1 (DO), LED204.3 (DI)
unnamed: LED204.1 (DO), LED205.3 (DI)
unnamed: LED205.1 (DO), LED206.3 (DI)
unnamed: LED206.1 (DO), LED207.3 (DI)
unnamed: LED207.1 (DO), LED208.3 (DI)
unnamed: LED208.1 (DO), LED209.3 (DI)
unnamed: TP201.1, U201.39 (IO1)
unnamed: TP202.1, U201.38 (IO2)
unnamed: TP203.1, U201.15 (IO3)
unnamed: TP204.1, U201.4 (IO4)
unnamed: TP205.1, U201.5 (IO5)
unnamed: TP206.1, U201.6 (IO6)
unnamed: TP207.1, U201.7 (IO7)

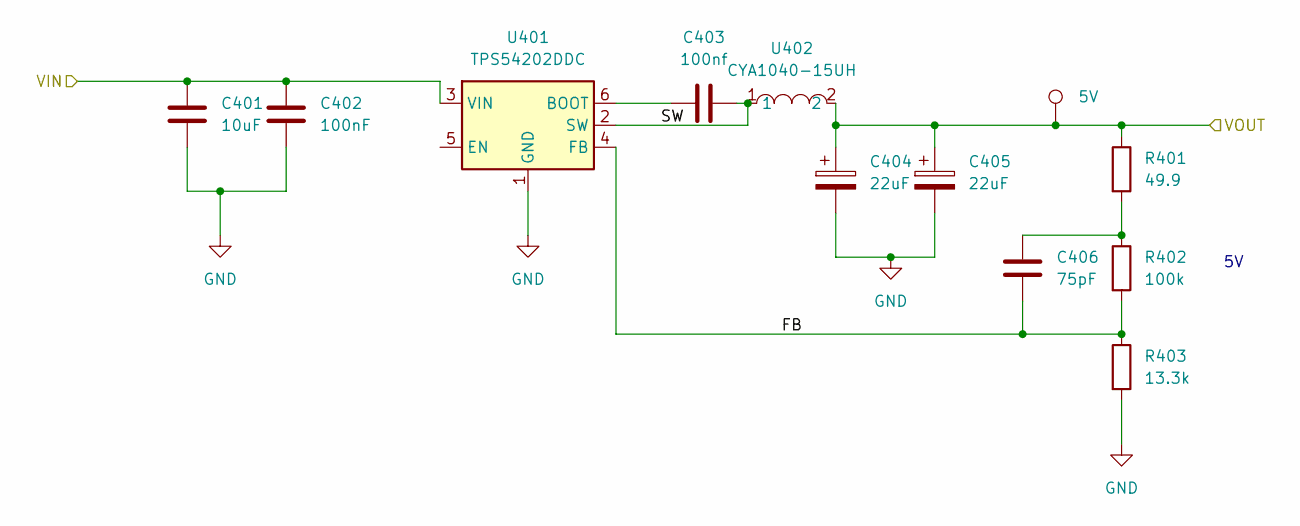
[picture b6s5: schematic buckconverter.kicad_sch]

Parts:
C401: 10uF; C_0603_1608Metric
C402: 100nF; C_0603_1608Metric
C403: 100nf; C_0603_1608Metric
C404, C405: 22uF; C_Elec_5x5.8; LCSC Part C336246
C406: 75pF; C_0603_1608Metric
R401: 49.9; R_0603_1608Metric
R402: 100k; R_0603_1608Metric
R403: 13.3k; R_0603_1608Metric
TP401: LabeledTestPoint
U401: TPS54202DDC; SOT-23-6
U402: CYA1040-15UH; IND-SMD_L11.6-W10.1; LCSC Part C6364678

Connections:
/5V: C404.1, C405.1, R401.1, TP401.1, U402.2; also elsewhere on the board
/20V: C401.1, C402.1, U401.3 (VIN); also elsewhere on the board
/buckconverter/FB: C406.1, R402.2, R403.1, U401.4 (FB)
/buckconverter/SW: C403.2, U401.2 (SW), U402.1
GND: C401.2, C402.2, C404.2, C405.2, R403.2, U401.1 (GND); also elsewhere on the board
unnamed: C406.2, R401.2, R402.1
unnamed: C403.1, U401.6 (BOOT)
